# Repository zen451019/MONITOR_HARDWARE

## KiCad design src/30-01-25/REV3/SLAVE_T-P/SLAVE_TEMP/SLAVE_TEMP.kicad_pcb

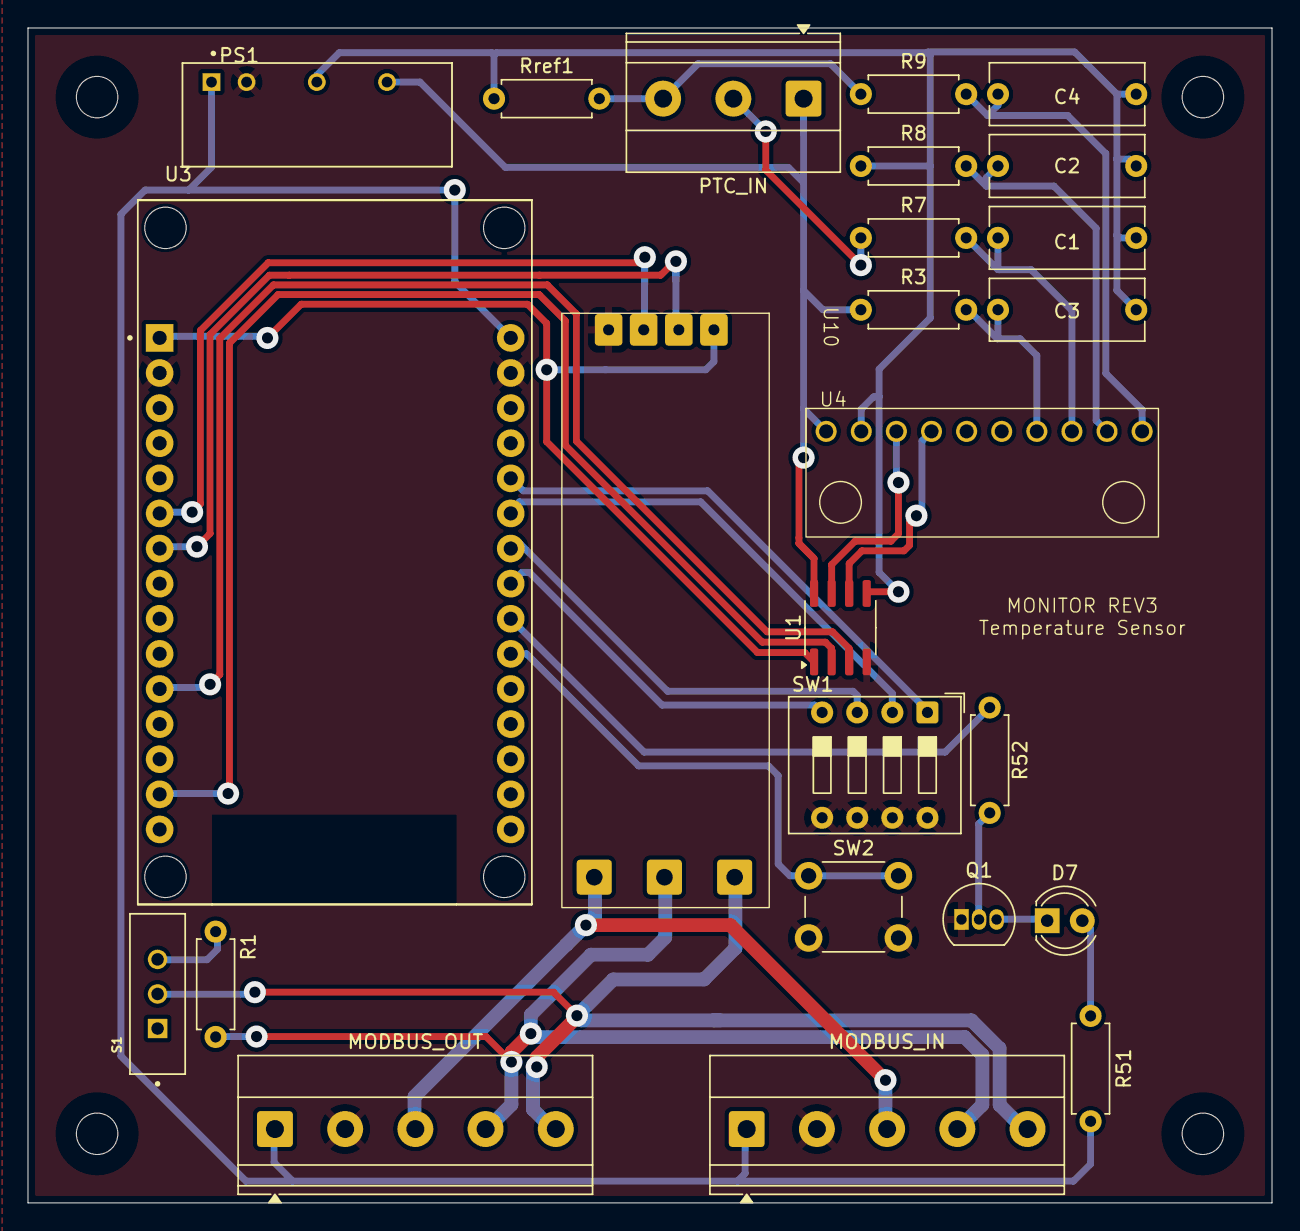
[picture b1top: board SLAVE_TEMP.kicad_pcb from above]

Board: 2 copper layers, 90.0 x 85.0 mm, 25 parts (0 on the bottom side), 30 nets.

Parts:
C1, C2, C3, C4: 100nF; C_Rect_L11.0mm_W4.3mm_P10.00mm_MKT
D7: LED; LED_D4.0mm
MODBUS_IN: SCREW_TERMINAL_5; TerminalBlock_Phoenix_MKDS-1,5-5-5.08_1x05_P5.08mm_Horizont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
MODBUS_OUT: SCREW_TERMINAL_5; TerminalBlock_Phoenix_MKDS-1,5-5-5.08_1x05_P5.08mm_Horizont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
PS1: TMH_0505S; CONV_TMH_0505S
PTC_IN: SCREW_TERMINAL_3; TerminalBlock_Phoenix_MKDS-1,5-3-5.08_1x03_P5.08mm_Horizont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
Q1: PN2222A; TO-92_Inline
R1, R51: 330; R_Axial_DIN0207_L6.3mm_D2.5mm_P7.62mm_Horizontal
R3, R7, R8, R9: 1K; R_Axial_DIN0207_L6.3mm_D2.5mm_P7.62mm_Horizontal
R52: 3.3k; R_Axial_DIN0207_L6.3mm_D2.5mm_P7.62mm_Horizontal
Rref1: 1K; R_Axial_DIN0207_L6.3mm_D2.5mm_P7.62mm_Horizontal
S1: MINI-SPDT-SW; SW_MINI-SPDT-SW
SW1: SW_DIP_x04; SW_DIP_SPSTx04_Slide_9.78x12.34mm_W7.62mm_P2.54mm
SW2: SW_Push; SW_PUSH_6mm
U1: ADuM1201AR; SOIC-8_3.9x4.9mm_P1.27mm
U3: ESP32-DEVKIT-V1; MODULE_ESP32_DEVKIT_V1
U4: ADS1015
U10: RS485_TRANSCEIVER; XY-017

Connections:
3V3: U1.1 (VDD1), U3.1 (3V3), U10.1 (VCC)
5V: MODBUS_IN.1, MODBUS_OUT.1, PS1.1 (+VIN(VCC)), R51.1, U3.30 (VIN)
5V_ISO: PS1.6 (+VOUT), PTC_IN.1, R3.1, U1.8 (VDD2), U4.8 (VDD)
485+: MODBUS_IN.5, MODBUS_OUT.5, S1.2, U10.5 (A)
485-: MODBUS_IN.4, MODBUS_OUT.4, R1.2, U10.6 (B)
BUTTOM: SW2.1, U3.21 (D32)
DIP_1: SW1.1, U3.26 (D14)
DIP_2: SW1.2, U3.25 (D27)
DIP_3: SW1.3, U3.24 (D26)
DIP_4: SW1.4, U3.23 (D25)
GND: MODBUS_IN.2, MODBUS_OUT.2, PS1.2 (-VIN(GND)), Q1.1 (E), SW1.5, SW1.6, SW1.7, SW1.8, SW2.2, U1.4 (GND1), U3.2 (GND), U3.29 (GND), U10.4 (GND)
GND_ISO: C1.1, C2.1, C3.1, C4.1, PS1.4 (-VOUT), R8.1, Rref1.1, U1.5 (GND2), U4.3 (GND)
GND_T: MODBUS_IN.3, MODBUS_OUT.3, U10.7 (GND)
LED: R52.2, U3.22 (D33)
unnamed: D7.2 (A), R51.2
unnamed: D7.1 (K), Q1.3 (C)
unnamed: Q1.2 (B), R52.1
unnamed: R1.1, S1.3
RX: U3.6 (RX2), U10.3 (RXD)
SCL: U1.2 (VOA), U3.14 (D22)
SCL_H: U1.7 (VIA), U4.10 (SCL)
SDA: U1.3 (VIB), U3.11 (D21)
SDA_H: U1.6 (VOB), U4.9 (SDA)
SIGNAL_2: PTC_IN.2, R7.1
SIGNAL_4: PTC_IN.3, R9.1, Rref1.2
SIGNAL_OUT1: C3.2, R3.2, U4.4 (AIN0)
SIGNAL_OUT2: C1.2, R7.2, U4.5 (AIN1)
SIGNAL_OUT3: C2.2, R8.2, U4.6 (AIN2)
SIGNAL_OUT4: C4.2, R9.2, U4.7 (AIN3)
TX: U3.7 (TX2), U10.2 (TXD)
